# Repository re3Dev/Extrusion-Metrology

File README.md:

Copyright © 2026 Mitchell Mashburn All rights reserved.
Source files are made publicly available for review, education, and evaluation. No permission is granted for commercial manufacture, redistribution, or derivative works without written authorization.

# Extrusion-Metrology
PCB with a main purpose of a low-cost, dedicated 1D metrology sensor specifically for a Klipper printer, use controlled illumination to get a high-resolution bead cross-section without running full machine vision, and automate calibration using the printer's existing motion system.

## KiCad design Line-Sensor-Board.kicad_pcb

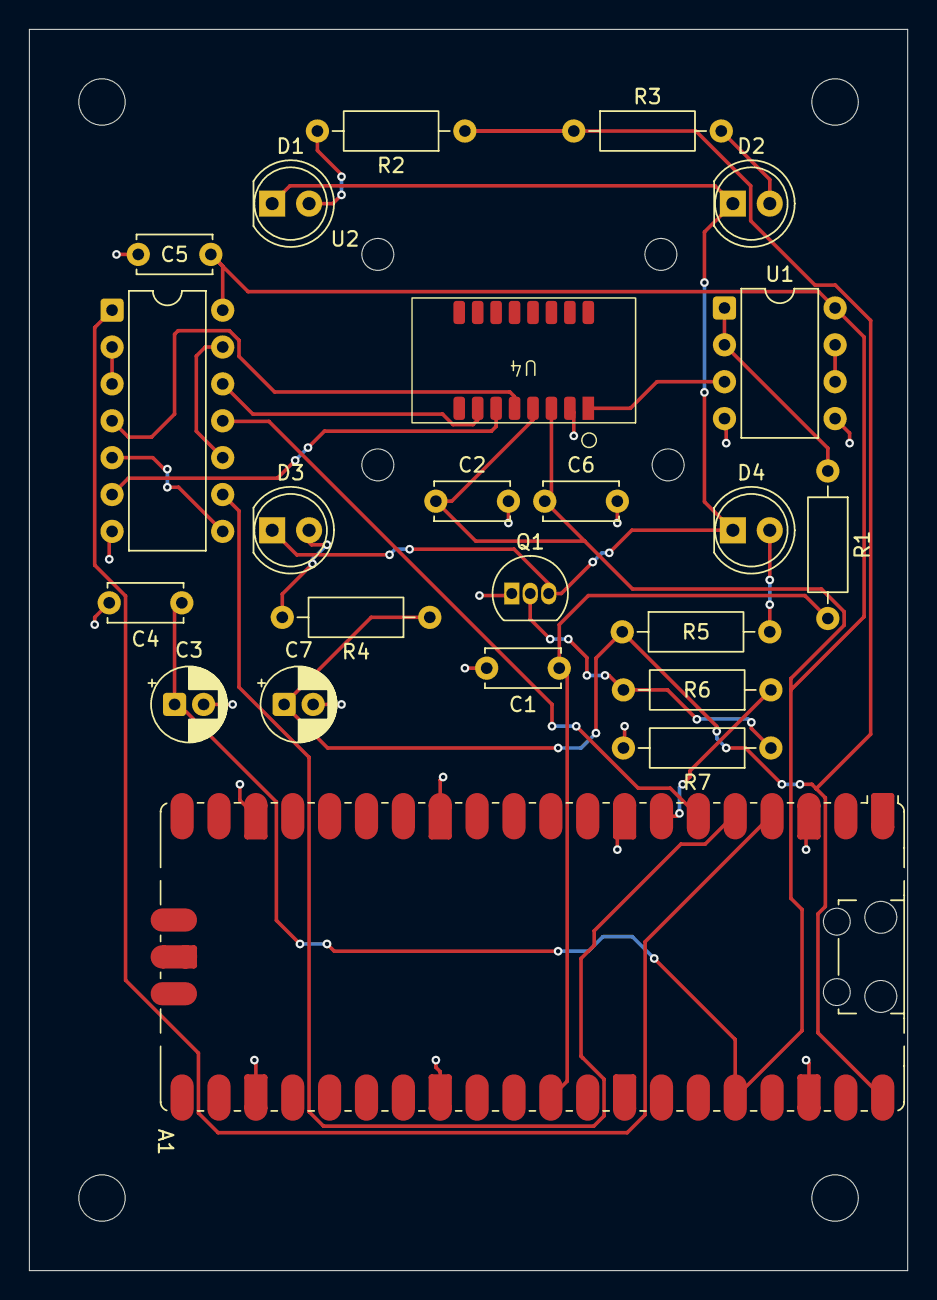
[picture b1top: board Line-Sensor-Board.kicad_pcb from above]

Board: 2 copper layers, 60.5 x 85.5 mm, 23 parts (0 on the bottom side), 23 nets.

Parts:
A1: RaspberryPi_Pico; RaspberryPi_Pico_SMD_HandSolder
C1: 1nF; C_Disc_D5.0mm_W2.5mm_P5.00mm
C2, C4, C5, C6: 100nF; C_Disc_D5.0mm_W2.5mm_P5.00mm
C3: 10µF; CP_Radial_D5.0mm_P2.00mm
C7: 10 µF; CP_Radial_D5.0mm_P2.00mm
D1, D2, D3, D4: LED; LED_D5.0mm
Q1: PN2222A; TO-92_Inline
R1: 100R; R_Axial_DIN0207_L6.3mm_D2.5mm_P10.16mm_Horizontal
R2, R3, R4, R5: 150R; R_Axial_DIN0207_L6.3mm_D2.5mm_P10.16mm_Horizontal
R6: 1K; R_Axial_DIN0207_L6.3mm_D2.5mm_P10.16mm_Horizontal
R7: 10K; R_Axial_DIN0207_L6.3mm_D2.5mm_P10.16mm_Horizontal
U1: MCP6022; DIP-8_W7.62mm
U2: 74HC04; DIP-14_W7.62mm
U4: TCD1103GFG_HandSolder

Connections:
+3.3V: A1.36 (3V3), C2.1, C3.1, C4.1, C5.1, C6.1, U1.8 (V+), U2.14 (VCC), U4.3 (VAD), U4.4 (VDD)
/CCD_ADC: A1.31 (GPIO26_ADC0), C1.1, R1.2
/CCD_OS: U1.3 (+), U4.1 (OS)
/GP2: A1.4 (GPIO2), U2.1
/GP3: A1.5 (GPIO3), U2.9
/GP4: A1.6 (GPIO4), U2.11
/ICG: U2.6, U4.6 (ICG)
/LED_5V: A1.40 (VBUS), C7.1, R2.1, R3.1, R4.1, R5.1
/LED_CATHODES: D1.1 (K), D2.1 (K), D3.1 (K), D4.1 (K), Q1.3 (C)
/LED_ENABLE: A1.7 (GPIO5), R6.1
/PHIM: U2.4, U4.5 (PHIM)
/SH: U2.12, U4.7 (SH)
GND: A1.3 (GND), A1.8 (GND), A1.13 (GND), A1.18 (GND), A1.23 (GND), A1.28 (GND), A1.38 (GND), C1.2, C2.2, C3.2, C4.2, C5.2, C6.2, C7.2, Q1.1 (E), R7.2, U1.4 (V-), U1.5 (+), U2.7 (GND), U4.2 (SS)
unnamed: D1.2 (A), R2.2
unnamed: D2.2 (A), R3.2
unnamed: D3.2 (A), R4.2
unnamed: D4.2 (A), R5.2
unnamed: Q1.2 (B), R6.2, R7.1
unnamed: R1.1, U1.1, U1.2 (-)
unnamed: U1.6 (-), U1.7
unnamed: U2.2, U2.3
unnamed: U2.5, U2.8
unnamed: U2.10, U2.13
